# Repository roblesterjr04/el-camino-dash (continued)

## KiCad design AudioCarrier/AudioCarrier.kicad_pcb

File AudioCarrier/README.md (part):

# Audio card

A **slot card** for the DigiDash rev 2 board: **80 × 60 mm**, standing on edge in a 2×15 slot, its right-angle header
on the bottom edge and its jacks on the top edge (`docs/hardware/accessory_ports.md`, rev 2 section). It goes in
**slot 1**: the RCA block is 26.5 mm tall, and slot 1 is the one whose parts side faces off the end of the row. It is
the clock master of the slot's **I2S rail**, which reaches every other slot (an AI voice card can go in any of them). The directory keeps its old name. On it:
- an **ESP32-DevKitC-VE** (the bench board: ESP32-WROVER-E, classic ESP32 for A2DP + AVRCP + HFP; 8 MB flash, 8 MB
  PSRAM, PCB antenna) plugged into two 1 × 19 female sockets. It brings its own USB programming and 3.3 V regulator,
  so the card has no module, regulator, buttons or programming header to assemble (rev J)
- two **TI PCM5102A** stereo DACs (front pair, rear pair)
- a **TI PCM1808** ADC with an electret microphone preamp (hands-free calls)
- a **2 × 2 right-angle RCA block** (Kycon KLP42X-61-WW/RR) and, beside it on the same top edge, a small
  **3.5 mm jack** (Same Sky SJ1-3533NG, through-hole) for a hands-free car microphone (no line / aux input)
- a **74LVC125** that puts the I2S clocks, the mic data and MCLK on the slot's link lines, for the partner card

CAN node from its slot (`0x14 + (slot − 1)`: `0x14` in slot 1), 5 V from the slot only. It fits rev 2 only (the 2×5 rev 1 version is in git history).

| Files | |
| --- | --- |
| `AudioCarrier.kicad_sch` / `.kicad_pcb` / `.kicad_pro` | The card: 80 × 60 mm, 2 layers, every part on the top. Placed and routed (see [Status](#status)). KiCad 10 |
| `AudioCarrier.pretty` | The DevKitC socket footprint (pin positions and numbers as Espressif's own `Espressif.pretty/ESP32-DevKitC`, rows 25.4 mm apart) and the RCA block (hole pattern from Kycon's KLP42X-61-xx/xx drawing), and a plain 3D model of the block. Everything else is stock KiCad (the jack: `Connector_Audio:Jack_3.5mm_CUI_SJ1-3533NG_Horizontal`) |
| `generate/` | Scripts that produced the files (`gen_footprints.py`, `gen_sch.py`, `gen_pcb.py`, `drc.py`) |

## Signal paths

```
ESP32 I2S0 (master) BCK GPIO14, WS GPIO25, DOUT GPIO27 ──► PCM5102A front ──► 470 R + 2.2 nF ──► J2 FL, J3 FR
ESP32 I2S1 (slave, same BCK / WS)  DOUT GPIO26            ──► PCM5102A rear  ──► 470 R + 2.2 nF ──► J4 RL, J5 RR
+5VA ─ 1k ─ MICV (47u) ─ 2.2k ─┐
J6 tip, electret mic (100p) ────┴ 1u ─ TLV9062 A (gain 22.4) ─ 1u ─► PCM1808 VINL ──► ESP32 I2S0 DIN GPIO35
J6 ring + sleeve = GND;  PCM1808 VINR ─ 1u ─ GND;  TLV9062 B = follower on VMID (spare)
ESP32 GPIO0 (CLK_OUT) 12.288 MHz = 256 fS master clock ──► 33 R ──► PCM1808 SCKI   GPIO4 = DAC mute (XSMT, pulled low)

I2S rail (bused to all six slots), through U8 74LVC125 (enabled by GPIO21 low) and 33 R each. The card's net names
are LINK0-4; on the main board they are the rail's I2S_* nets:
  BCK ──► LINK0 = I2S_BCK    WS ──► LINK1 = I2S_WS    PCM1808 DOUT (mic) ──► LINK2 = I2S_MIC    MCLK ──► LINK4 = I2S_MCLK
  LINK3 = I2S_RET (the granted card's audio) ── 33 R ──► GPIO34 = I2S1 data in (100k pull-down)
Audio bus: FL_LINE / FR_LINE ── 100 R ──► AUDIO_L / AUDIO_R;  AUDIO_GND ── 10 R ── GND
Slot ID (pin 11): 10k to 3.3 V here, the slot's resistor to GND on the main board ──► GPIO36 (ADC1)
```

DevKitC-VE socket pins (U1; numbers as Espressif's KiCad symbol, `ESP32-DevKitC`). The GPIOs are the ones the
module version used, so the firmware's pin defines are unchanged:

| Pin | DevKitC | Net | Pin | DevKitC | Net |
| --- | --- | --- | --- | --- | --- |
| 1 | 3V3 | +3V3 (out of the DevKitC's regulator) | 19 | 5V | +5V from the slot |
| 14, 32, 38 | GND | GND | 25 | IO0 | MCLK (CLK_OUT1) → 33 R → PCM1808 SCKI, LINK4 (also the DevKitC BOOT strap) |
| 3 | VP (IO36) | SLOT_ID (ADC1) | 26 | IO4 | DAC_MUTE (XSMT, 100k down) |
| 5 | IO34 | LINK_SDIN (I2S1 data in, RET) | 33 | IO21 | LINK_EN_N (74LVC125 OEs, 10k up) |
| 6 | IO35 | ADC_DOUT (I2S0 data in) | 7 / 8 | IO32 / IO33 | CAN TXD / RXD (1k) |
| 9 | IO25 | I2S WS (both DACs, ADC, LINK1) | 10 | IO26 | I2S1 DOUT → rear DAC |
| 11 / 12 | IO27 / IO14 | I2S0 DOUT → front DAC / BCK (all, LINK0) | others | | open (EN, VN, 12, 13, 2, 5, 15, 18, 19, 22, 23, TX / RX; 6-11 flash, 16 / 17 PSRAM) |

| Jack (J2, the block) | Signal | Insert colour |
| --- | --- | --- |
| Left column, top | Front left (U5 OUTL) | white |
| Left column, bottom | Front right (U5 OUTR) | red |
| Right column, top | Rear left (U6 OUTL) | white |
| Right column, bottom | Rear right (U6 OUTR) | red |
| J6, 3.5 mm jack (Same Sky SJ1-3533NG) | tip = mic (pin T); ring (R) and sleeve (S) = GND, so a mono TS plug and a TRS plug both work | top edge, right of the block |

"Left" and "right" are seen from the plug side, standing outside the right edge. The sleeves and the front plate's two
solder tabs are ground.

- **DACs:** 3-wire I2S, SCK tied to ground so the internal PLL runs from BCK (BCK must be 64 fS, which is what the ESP32
  produces with 32-bit slots). FMT, FLT and DEMP low. Outputs are ground-centred 2.1 Vrms: no DC-block caps, just the
  datasheet's 470 R / 2.2 nF filter. The two DACs share BCK and LRCK and have their own data lines, so front and rear are
  independent (fader in software). Both stay muted until the firmware raises GPIO4. Decoupling as in the datasheet
  (LDOO 0.1 µF).
- **ADC:** slave mode (MD0 = MD1 = low), I2S 24-bit, 5 V analog / 3.3 V digital, full scale 3 Vp-p. It runs from the same
  BCK / LRCK as the DACs, so ESP32 I2S0 does full duplex (play + record) in master mode.
- **Mic input (calls only):** for an electret car hands-free microphone on a mono 3.5 mm TS plug ("plug-in power").
  Bias: 2.2 kΩ to the tip from MICV, which is +5VA through 1 kΩ + 47 µF (about 3 Hz; about 4.5 V at a 0.5 mA
  capsule). 100 pF from the tip to ground at the jack (RF). DC-blocked (1 µF into 100 kΩ to VMID = 2.5 V), then
  TLV9062 A non-inverting, gain 1 + 47k / 2.2k = 22.4 (27 dB; 2.2 kΩ + 10 µF to ground, so DC gain 1; 100 pF across
  the 47k, about 34 kHz). A -42 dBV/Pa capsule gives 0.18 Vrms at 94 dB SPL; the PCM1808's ~1 Vrms full scale is
  reached at about 109 dB SPL, so a loud voice close to the mic still has headroom. Out through 1 µF to VINL (the
  left channel, which the firmware reads). VINR is AC-grounded through 1 µF; TLV9062 B is a follower on VMID, its
  output unloaded (no floating inputs). There is no line / aux input.
- **Power:** +5 V from the port to the DevKitC's 5V pin (10 µF at the header). The DevKitC's own 3.3 V regulator
  runs the ESP32 and, from its 3V3 pin (100 nF there), the card's 3.3 V loads: the converters' digital sides, the
  buffer and the CAN VIO, some tens of mA. Ferrites make +5VA (ADC analog, op-amp, mic bias) and +3V3A (DAC analog
  and charge pump). **Do not plug the DevKitC's USB in while the card is powered from the slot**: both feed its 5V
  pin (check the DevKitC's schematic for a diode before relying on it). To program it in place, unpower the card.

## Board

- **Outline:** 80 × 60 mm, no mounting holes: the slot and the case hold it. The RCA block's plate has a hole in the
  middle of the four jacks; if it takes a screw to the case panel, plug forces go to the case and not the slot (check
  on the part: Kycon's drawing does not say).
- **Slot header (J1):** right-angle 2×15 (`PinHeader_2x15_P2.54mm_Horizontal`) on the parts side, centred on the bottom
  edge: pin 1 is 17.78 mm right of the centre (seen from the parts side, top edge up), the pins count to the left, the
  plastic body's outer face is on the bottom edge and the pins stand 6 mm past it. `gen_pcb.py` checks the orientation
  from the pads, so each pin meets the same-numbered pad of the main board's slot socket.
- **Top edge** (the case panel), from the left: the RCA block (centred at x 48, x 30.1–65.9 with its tabs) and the
  3.5 mm jack (x 72.3). These positions are constants at the top of `gen_pcb.py`; move them to suit the case.
- **DevKitC (U1):** two 1 × 19 female sockets (8.5 mm), rows 25.4 mm apart, lying along the card: pin 1 (3V3) at
  x 13.5, y 39.4, the J2 row (pins 1–19) at y 39.4 and the J3 row at y 14.0, from x 13.5 to 59.2. The DevKitC's PCB
  spans y ≈ 12.5–40.9; its **antenna end is at the left edge** and its **USB end points right** (x ≈ 61), over the
  DACs. It stands about 8.5 mm up on the sockets (module top ≈ 13.5 mm off the card, the USB plug higher), so low SMD
  parts sit under it. The module and its antenna reach past pin 1 toward the left edge: the footprint allows 13 mm
  (measure the -VE: Espressif's footprint shows the WROOM antenna 1.1–7.0 mm past pin 1), and the card keeps **no
  copper on either layer** from the left edge to x 12, y 12–41.5. Keep metal out of that end of the case. Housing: the
  card's left edge is board y 93, so the antenna is at y ≈ 81–93, z ≈ 22–55 (was the WROVER at the top corner).
- **RCA block (J2):** Kycon KLP42X-61-WW/RR (white on top, red below). The jacks face off the top edge (right-angle),
  and the plate's rear face is the board edge. The body is 34 mm wide and 10 mm deep behind the edge, and **26.5 mm
  tall** above the card (jack centres 6.7 and 20.7 mm up, columns 18 mm apart). The 1.0 mm plate and the barrels
  (7.8 mm) stand out past the edge. From the drawing (depths from the plate's front face): sleeve pins 1 / 4 at 7.0 mm,
  lower tips 3 / 6 at 10.25 mm, upper tips 2 / 5 at 11.5 mm, each column's pins 4 mm apart; two snap-in side tabs
  (2.4 mm wide, 7.5 mm deep, ±16.5 mm, barb to ±17.6 mm) in 1.9 × 3.0 mm slots, tied to ground. No switch contacts.
- **Mic jack (J6):** Same Sky SJ1-3533NG, through-hole, soldered by hand (KiCad's stock footprint, pins T / R / S),
  right of the block on the same edge. Its front face is on the edge (1.2 mm before the sleeve pin), body x 67.4–75.6
  and 14 mm deep behind the edge, its nose past the edge centred at x 72.3, where the SMT jack's was. It replaced the
  SJ-3523-SMT on 2026-11-19 so the card's connectors are all through-hole; the board was edited in place (footprint
  swapped, the jack's ground fan-outs dropped since its pins reach both pours, the tip re-routed on B to the old via).
- **Parts side (F):** every part. The DACs, ADC and op-amp sit right of the DevKitC's USB end (x 61–80), the CAN
  transceiver and the link buffer above the slot header, passives where the placer put them (some under the DevKitC).
- **Back (B):** copper and silkscreen only, no parts.
- **Assembly:** the fab places the SMD parts (one side). The through-hole parts (J1, J2, J6 and the two DevKitC sockets)
  are soldered by hand. They are marked **DNP** in the schematic and on the board (`DNP` in `gen_sch.py` /
  `gen_pcb.py`), so they stay out of the placement files, and the PCBWay BOM lists them as DNP lines
  ("do not place or buy").
- **Layers:** 2. F signal + GND pour, B GND pour + signal. 0.2 mm tracks, 0.3 mm on the supplies, 0.13 mm clearance,
  0.6 / 0.3 mm vias. Every SMD ground pin has its own via to the B pour; stitching vias tie the pours together.
- **Solder-mask dams:** U3 (VSSOP-8, 0.65 mm) has its pads narrowed to 0.43 mm so the gaps are 0.22 mm, enough for
  PCBWay to keep a mask dam (they rejected 0.15 mm on 2026-11-19). The TSSOPs are 0.25 mm as drawn. Run
  `python3 ../tools/mask_dams.py AudioCarrier` again after any regenerate (it is lost otherwise).

## Status

**Rev J (2026-11-19): the bench DevKitC-VE in sockets, 2 layers.** The WROVER-E module, the AP7361C regulator and
its capacitors (C1, C3), the module decoupling (C8, C9), the EN / BOOT parts (R2, R3, C10, SW1, SW2), the programming
header J10 and the unused node straps JP1 / JP2 are gone; the other reference numbers are unchanged. GPIO0's net is
now MCLK (was BOOT). Re-placed and re-routed by `gen_pcb.py --route` (GND left out of the router: the pours and
per-pin vias join it), then `mask_dams.py`, fill, DRC with the parity check: **0 errors, 0 unconnected**, 21
silkscreen warnings and U3's footprint-differs-from-library (the narrowed pads). 590 vias (64 GND fan-outs, 493
stitching), 109 track segments on B. Ten router vias 0.06–0.15 mm from an SMD pad were then nudged by hand (≤ 0.1 mm)
to ≥ 0.15 mm, PCBWay's via-off-pad rule; re-running `--route` does not reproduce that. Nothing in the antenna keep-out. The rev I notes that follow describe the
module version (in git).

**Schematic: done** (the slot card, 90 parts). **PCB: placed and routed** (2026-10-23, rev G): 80 × 60 mm, 4 layers, 90
placed parts (88 in the placement file: JP1 / JP2 are copper only). DRC with the schematic parity check: **no errors,
nothing unconnected, no footprint / parity errors**; 28 silkscreen warnings (text at the edge, over pads, overlapping) and one footprint-differs-from-library warning (U3, the mask-dam pads).
Rev H (2026-10-27): every part on F (single-sided assembly), re-placed and re-routed by `gen_pcb.py --route`
(120 passes); the ground stitching closed the one link Freerouting left. Two fan-out vias (R17 pad 2, R25 pad 1)
were then moved by hand to 0.15 mm clear of their pads, the PCBWay via-off-pad rule. 550 vias, none touching a pad;
nothing in the antenna keep-out. Fab outputs in `fab/`
(`python3 ../tools/fab_export.py AudioCarrier`); `fab/AudioCarrier_BOM_PCBWay.csv` is kept by hand and matches the
placement file; `AudioCarrier_BOM.csv` is the same list.
Rev I (2026-10-27): RCA block **Switchcraft PJRAS2X2S01X → Kycon KLP42X-61-WW/RR** (34 mm wide, 6 pins + 2 snap-in
tabs, 26.5 mm tall), centred at x 48 (was 52) so it clears the jack; re-placed and re-routed by `gen_pcb.py --route`.
Freerouting left /EN, /I2S_LRC and U8 pin 7 (GND) open and the finisher could not join them, so they were finished
by a one-off grid router (not in `generate/`): /EN a 5.5 mm F track by SW1; /I2S_LRC from U5 pin 15 through two vias
to U6's side, after lifting U5 pin 16's GND fan-out stub (pin 16 reaches the pours without it); U8 pin 7 a track and
a via to the plane. Ten Freerouting vias 0.137–0.146 mm from a pad were nudged (≤ 0.02 mm) to ≥ 0.15 mm, the PCBWay
via-off-pad rule. DRC with the parity check: **0 errors, 0 unconnected**, 28 silkscreen warnings; 546 vias, none
within 0.15 mm of a pad. Re-running `gen_pcb.py --route` does not reproduce these fixes. The finisher now checks
clearance only against items near each join (it hung for 20+ minutes on the full board).

- **Rev G (2026-10-23), before the PCBWay order:**
  - **Module:** ESP32-PICO-MINI-02-N8R2 (NRND) → **ESP32-WROVER-E-N8R8**. Footprint drawn from the datasheet v2.4
    (figure 15: 38 pads 1.5 × 0.9 on 1.27 mm, centres 17.5 mm apart, pin 1 7.44 mm from the antenna end, pin 19 1.1 mm
    from the far end; EPAD 3.7 mm square, 7.5 mm from the left edge and 16.16 mm from the far end, nine 0.9 mm paste
    openings, no vias in it). Pins checked against table 3. Same GPIOs as before (pin map above).
  - **Regulator:** AMS1117-3.3 + 22 µF tantalum → **AP7361C-33E-13** with ceramics (pinout 1 IN, 2 GND, 3 OUT, from
    the Diodes datasheet); tab solid to a ground copper area with 12 vias.
  - **Mic:** aux path removed (ring buffer, its coupling cap and bias resistor, the RING net); bias now from +5VA
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
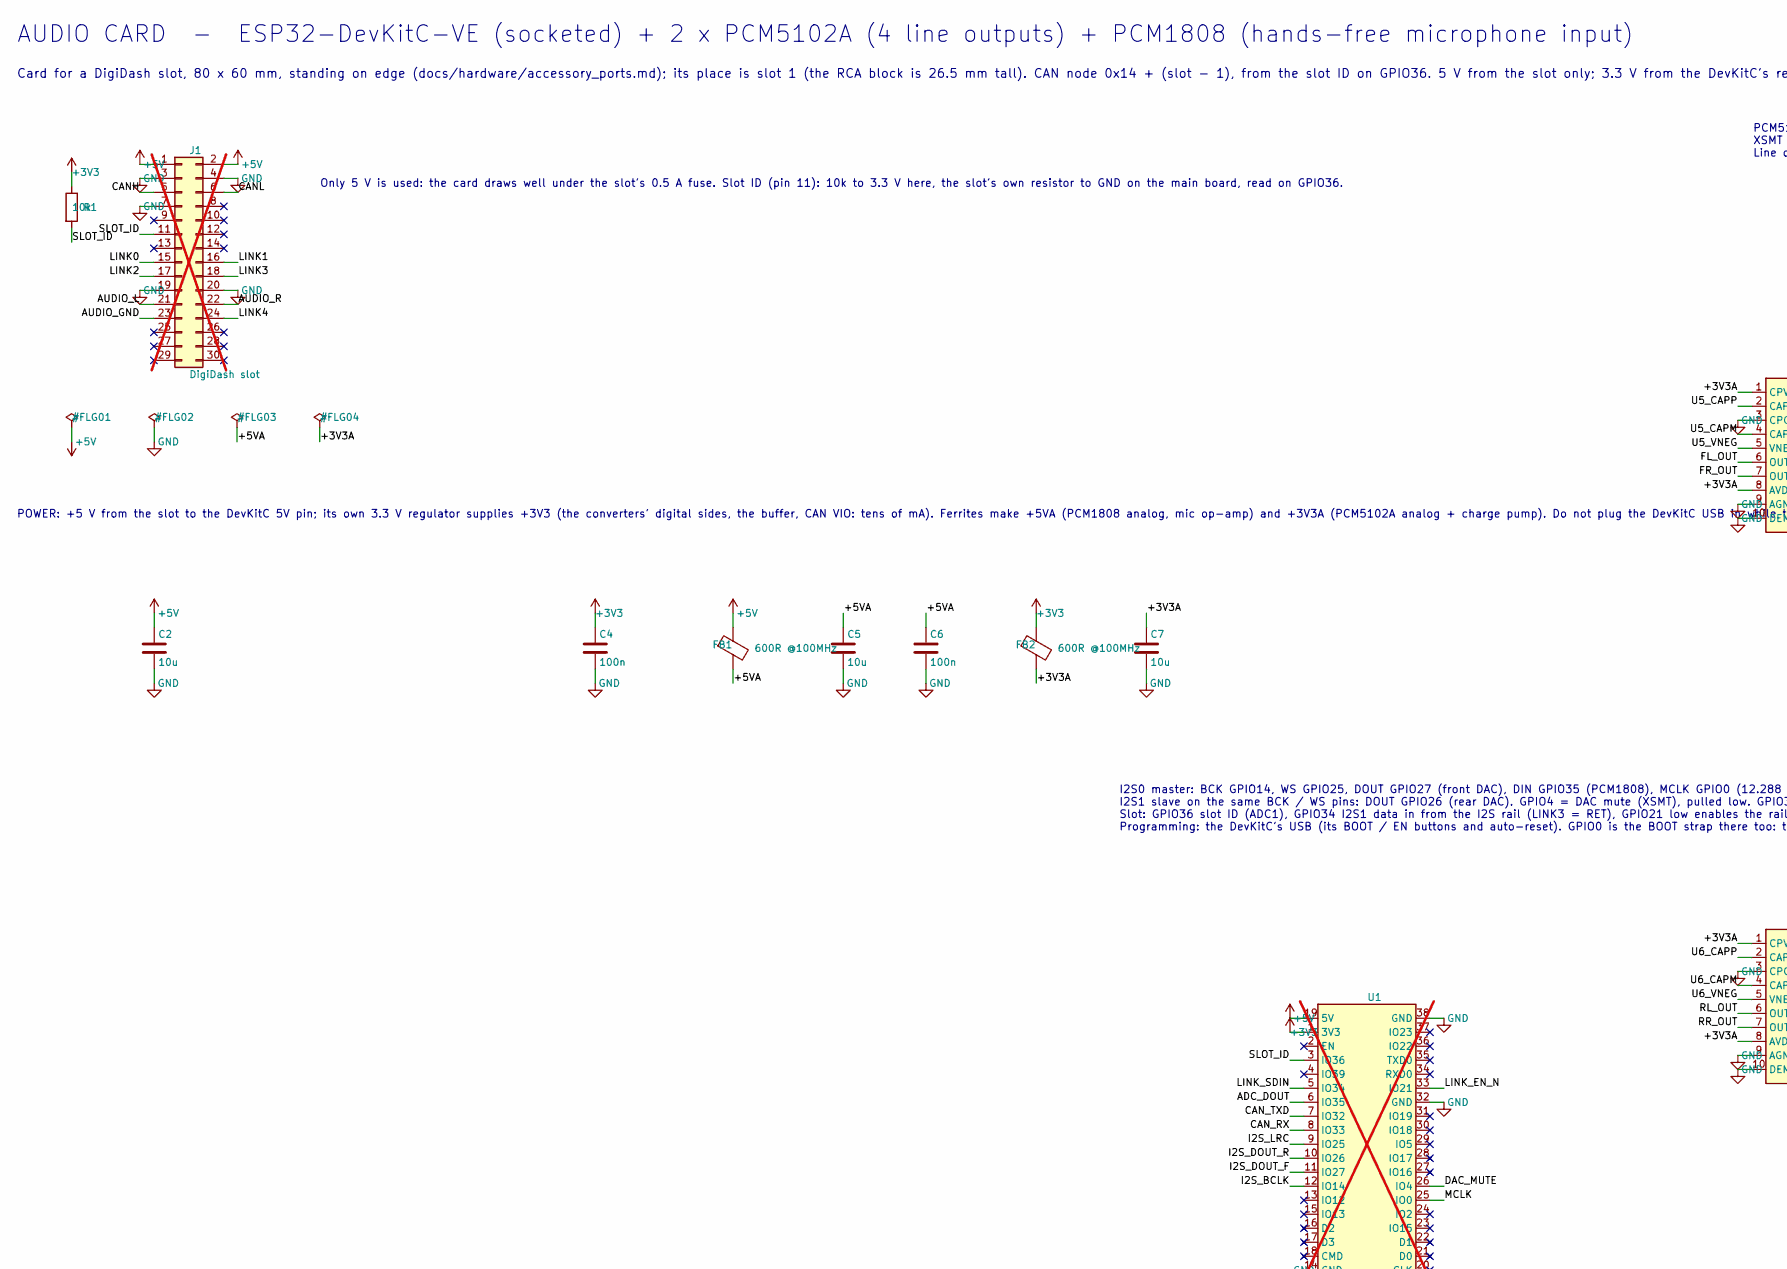
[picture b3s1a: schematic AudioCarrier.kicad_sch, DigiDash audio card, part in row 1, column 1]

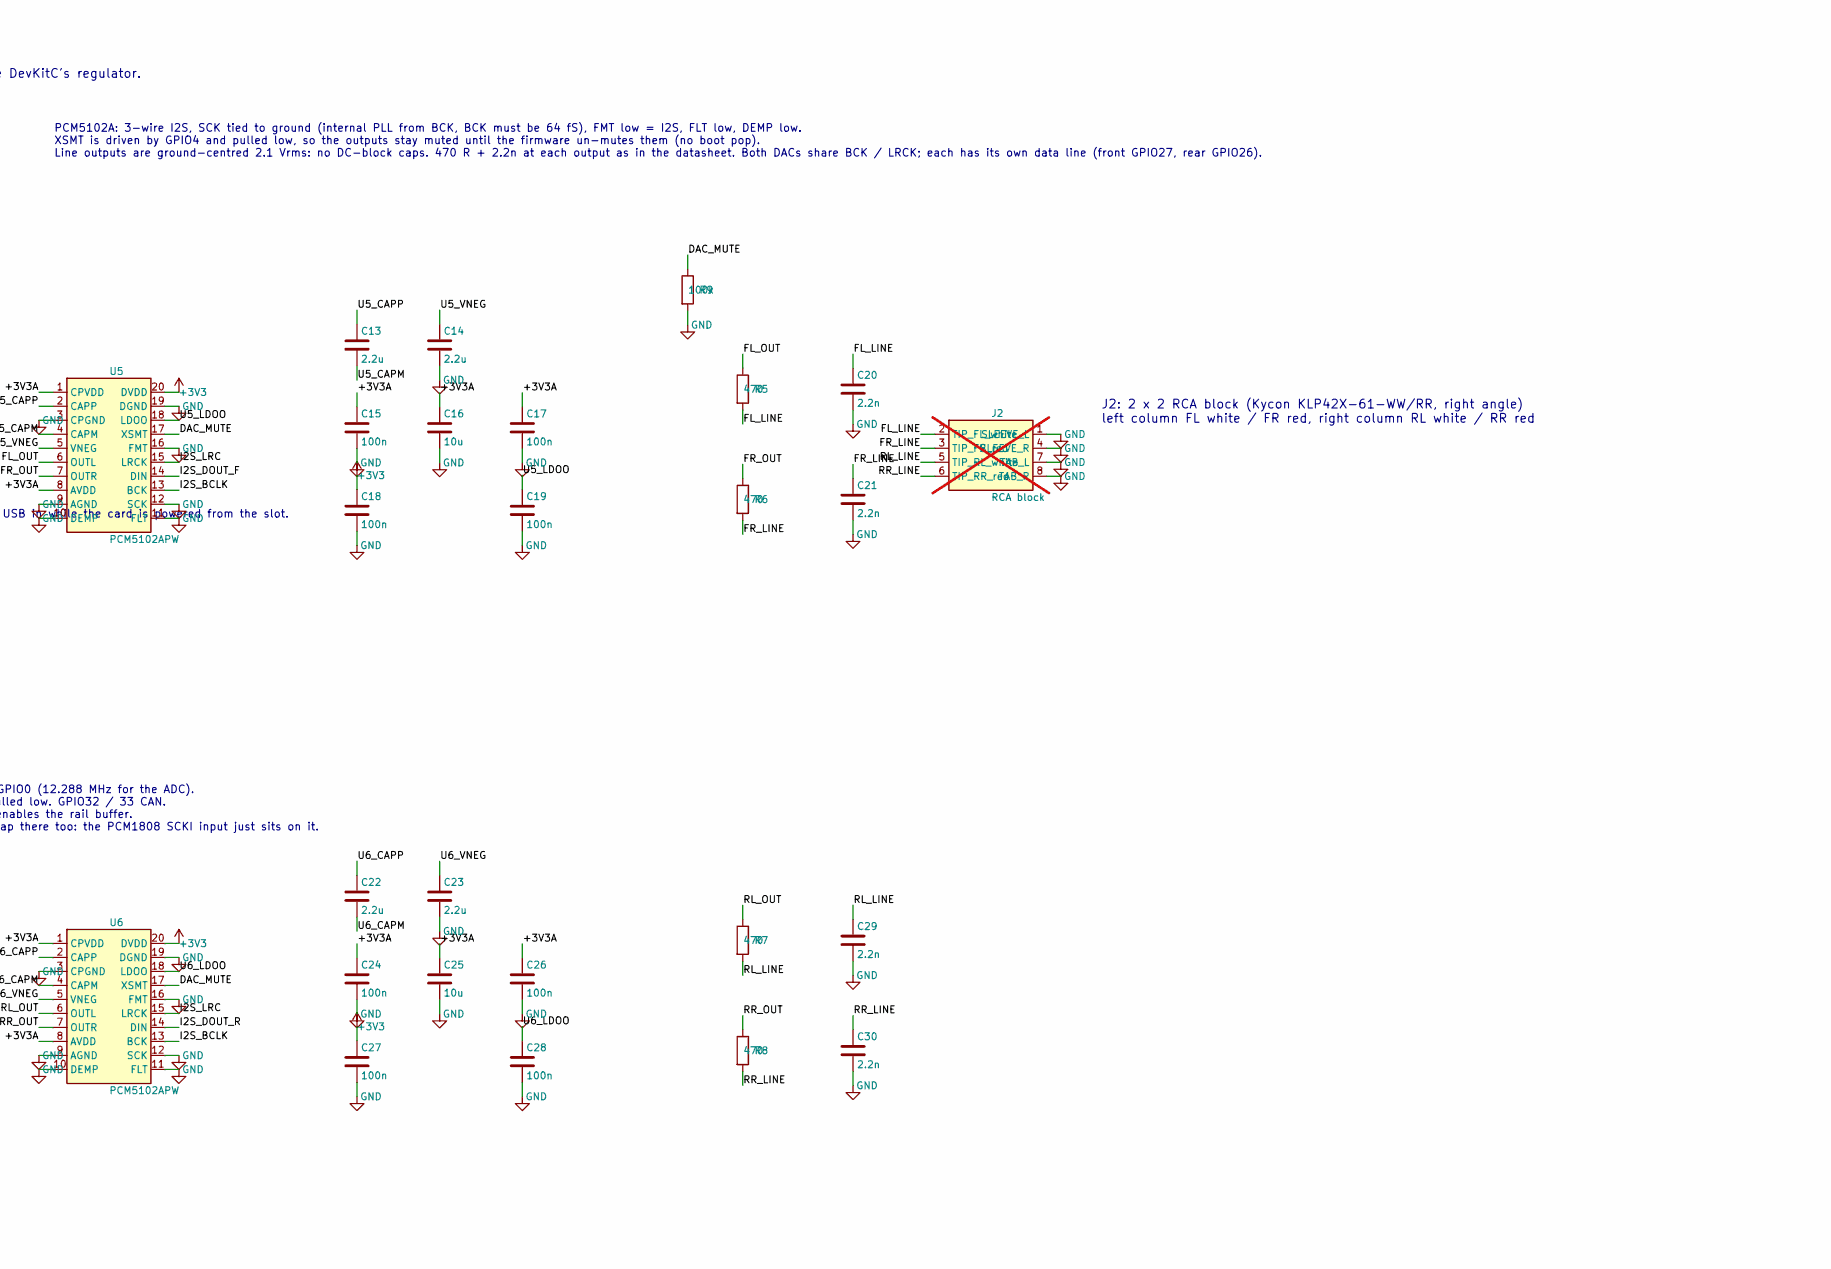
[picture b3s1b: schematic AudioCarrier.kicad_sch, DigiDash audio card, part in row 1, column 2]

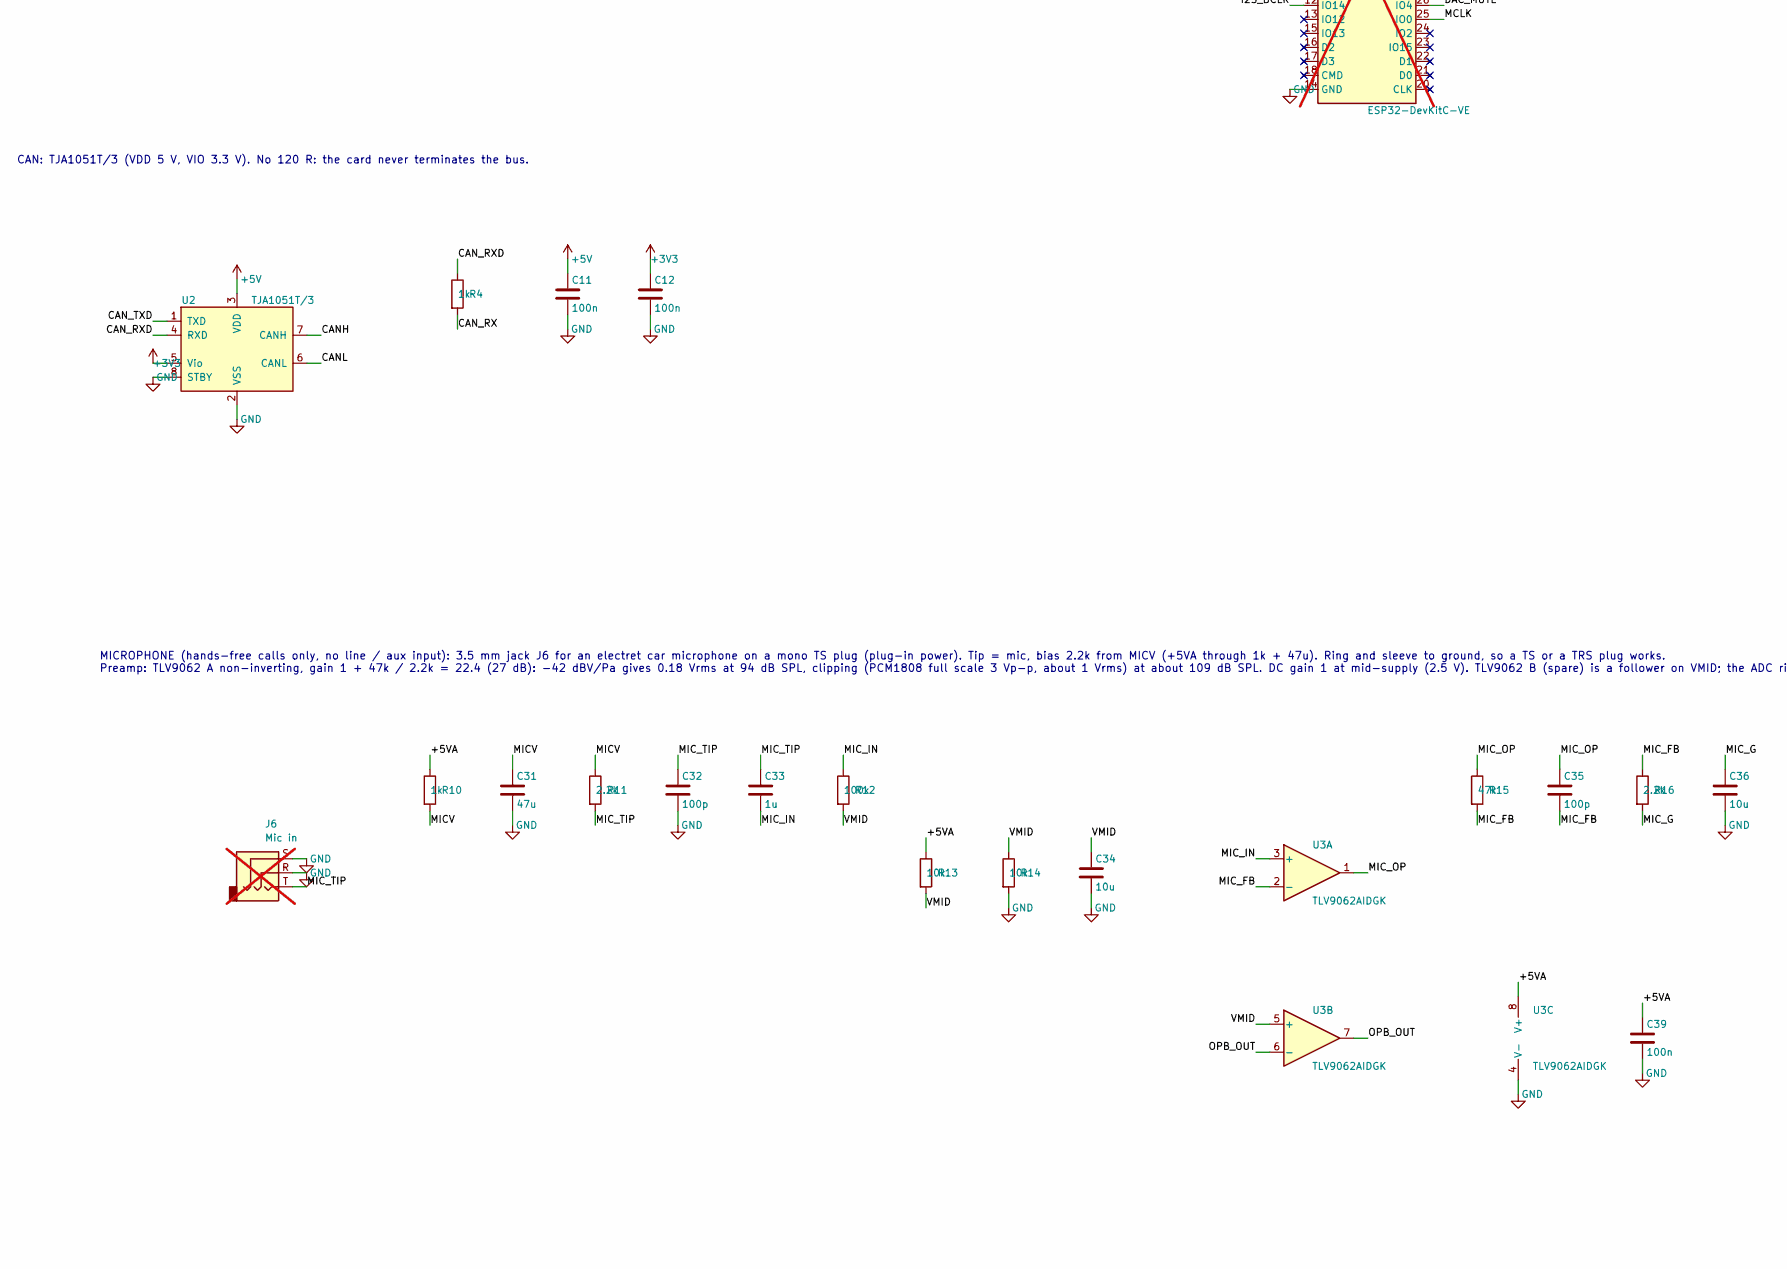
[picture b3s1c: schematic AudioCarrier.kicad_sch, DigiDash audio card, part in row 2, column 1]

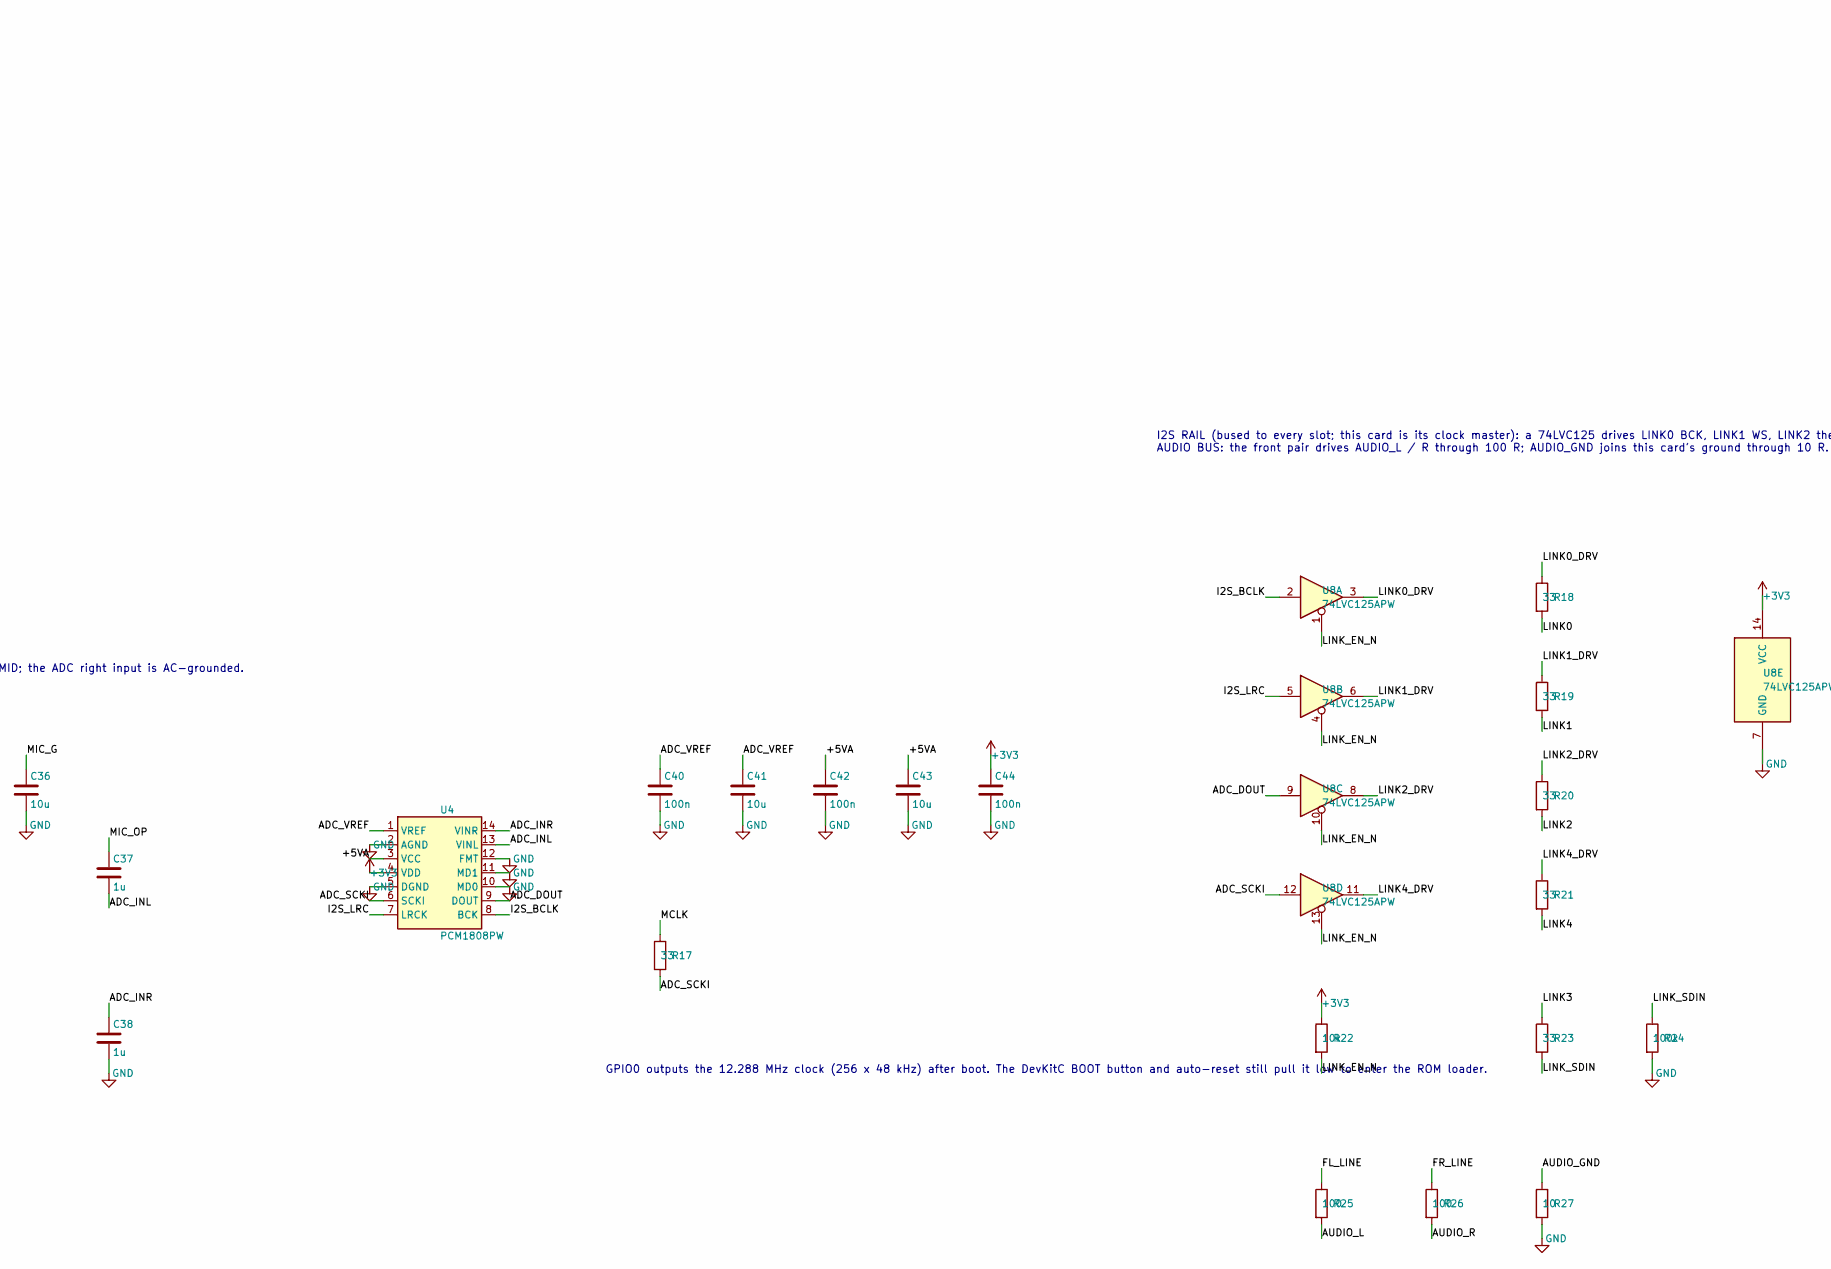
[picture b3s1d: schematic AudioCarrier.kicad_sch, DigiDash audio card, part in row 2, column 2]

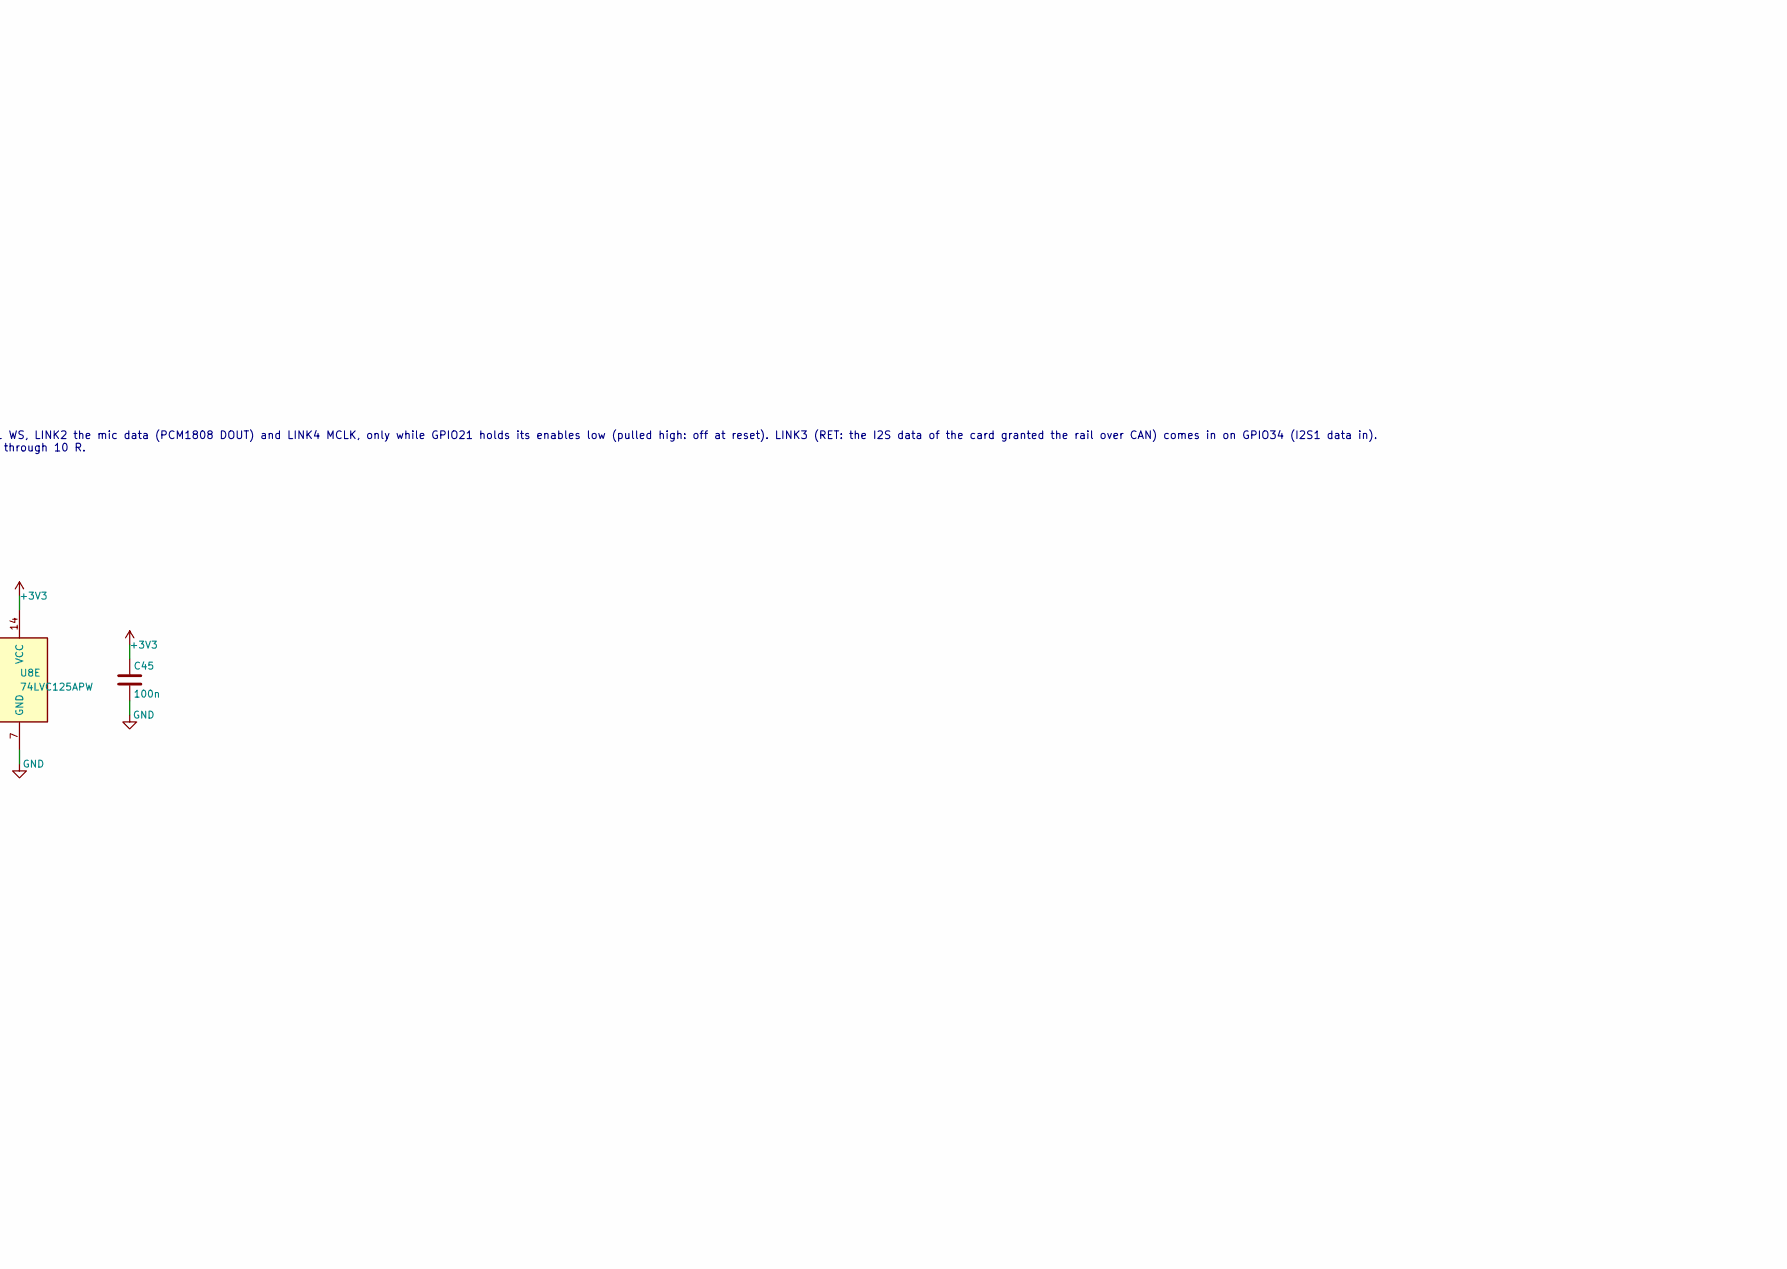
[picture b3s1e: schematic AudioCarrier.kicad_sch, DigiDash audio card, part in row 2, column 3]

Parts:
C2, C5, C7, C16, C25, C34, C36, C41, C43: 10u; C_0603_1608Metric
C4, C6, C11, C12, C15, C17, C18, C19, C24, C26, C27, C28, C39, C40, C42, C44, C45: 100n; C_0603_1608Metric
C13, C14, C22, C23: 2.2u; C_0603_1608Metric
C20, C21, C29, C30: 2.2n; C_0603_1608Metric
C31: 47u; C_1206_3216Metric
C32, C35: 100p; C_0603_1608Metric
C33, C37, C38: 1u; C_0603_1608Metric
FB1, FB2: 600R @100MHz; L_0603_1608Metric
J1: DigiDash slot; PinHeader_2x15_P2.54mm_Horizontal; not fitted
J2: RCA block; RCA_Kycon_KLP42X-61_RightAngle; not fitted
J6: Mic in; Jack_3.5mm_CUI_SJ1-3533NG_Horizontal; not fitted
R1, R13, R14, R22: 10k; R_0603_1608Metric
R4, R10: 1k; R_0603_1608Metric
R5, R6, R7, R8: 470; R_0603_1608Metric
R9, R12, R24: 100k; R_0603_1608Metric
R11, R16: 2.2k; R_0603_1608Metric
R15: 47k; R_0603_1608Metric
R17, R18, R19, R20, R21, R23: 33; R_0603_1608Metric
R25, R26: 100; R_0603_1608Metric
R27: 10; R_0603_1608Metric
U1: ESP32-DevKitC-VE; ESP32-DevKitC_Socket; not fitted
U2: TJA1051T/3; SOIC-8_3.9x4.9mm_P1.27mm
U3: TLV9062AIDGK; VSSOP-8_3x3mm_P0.65mm
U4: PCM1808PW; TSSOP-14_4.4x5mm_P0.65mm
U5, U6: PCM5102APW; TSSOP-20_4.4x6.5mm_P0.65mm
U8: 74LVC125APW; TSSOP-14_4.4x5mm_P0.65mm

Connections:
+3V3: C4.1, C12.1, C18.1, C27.1, C44.1, C45.1, FB2.1, R1.1, R22.1, U1.1 (3V3), U2.5 (Vio), U4.4 (VDD), U5.20 (DVDD), U6.20 (DVDD), U8.14 (VCC)
+5V: C2.1, C11.1, FB1.1, J1.1, J1.2, U1.19 (5V), U2.3 (VDD)
/+3V3A: C7.1, C15.1, C16.1, C17.1, C24.1, C25.1, C26.1, FB2.2, U5.1 (CPVDD), U5.8 (AVDD), U6.1 (CPVDD), U6.8 (AVDD)
/+5VA: C5.1, C6.1, C39.1, C42.1, C43.1, FB1.2, R10.1, R13.1, U3.8 (V+), U4.3 (VCC)
/ADC_DOUT: U1.6 (IO35), U4.9 (DOUT), U8.9
/ADC_INL: C37.2, U4.13 (VINL)
/ADC_INR: C38.1, U4.14 (VINR)
/ADC_SCKI: R17.2, U4.6 (SCKI), U8.12
/ADC_VREF: C40.1, C41.1, U4.1 (VREF)
/AUDIO_GND: J1.23, R27.1
/AUDIO_L: J1.21, R25.2
/AUDIO_R: J1.22, R26.2
/CANH: J1.5, U2.7 (CANH)
/CANL: J1.6, U2.6 (CANL)
/CAN_RX: R4.2, U1.8 (IO33)
/CAN_RXD: R4.1, U2.4 (RXD)
/CAN_TXD: U1.7 (IO32), U2.1 (TXD)
/DAC_MUTE: R9.1, U1.26 (IO4), U5.17 (XSMT), U6.17 (XSMT)
/FL_LINE: C20.1, J2.2 (TIP_FL_white), R5.2, R25.1
/FL_OUT: R5.1, U5.6 (OUTL)
/FR_LINE: C21.1, J2.3 (TIP_FR_red), R6.2, R26.1
/FR_OUT: R6.1, U5.7 (OUTR)
/I2S_BCLK: U1.12 (IO14), U4.8 (BCK), U5.13 (BCK), U6.13 (BCK), U8.2
/I2S_DOUT_F: U1.11 (IO27), U5.14 (DIN)
/I2S_DOUT_R: U1.10 (IO26), U6.14 (DIN)
/I2S_LRC: U1.9 (IO25), U4.7 (LRCK), U5.15 (LRCK), U6.15 (LRCK), U8.5
/LINK0: J1.15, R18.2
/LINK0_DRV: R18.1, U8.3
/LINK1: J1.16, R19.2
/LINK1_DRV: R19.1, U8.6
/LINK2: J1.17, R20.2
/LINK2_DRV: R20.1, U8.8
/LINK3: J1.18, R23.1
/LINK4: J1.24, R21.2
/LINK4_DRV: R21.1, U8.11
/LINK_EN_N: R22.2, U1.33 (IO21), U8.1, U8.4, U8.10, U8.13
/LINK_SDIN: R23.2, R24.1, U1.5 (IO34)
/MCLK: R17.1, U1.25 (IO0)
/MICV: C31.1, R10.2, R11.1
/MIC_FB: C35.2, R15.2, R16.1, U3.2 (-)
/MIC_G: C36.1, R16.2
/MIC_IN: C33.2, R12.1, U3.3 (+)
/MIC_OP: C35.1, C37.1, R15.1, U3.1
/MIC_TIP: C32.1, C33.1, J6.T, R11.2
/OPB_OUT: U3.6 (-), U3.7
/RL_LINE: C29.1, J2.5 (TIP_RL_white), R7.2
/RL_OUT: R7.1, U6.6 (OUTL)
/RR_LINE: C30.1, J2.6 (TIP_RR_red), R8.2
/RR_OUT: R8.1, U6.7 (OUTR)
/SLOT_ID: J1.11, R1.2, U1.3 (IO36)
/U5_CAPM: C13.2, U5.4 (CAPM)
/U5_CAPP: C13.1, U5.2 (CAPP)
/U5_LDOO: C19.1, U5.18 (LDOO)
/U5_VNEG: C14.1, U5.5 (VNEG)
/U6_CAPM: C22.2, U6.4 (CAPM)
/U6_CAPP: C22.1, U6.2 (CAPP)
/U6_LDOO: C28.1, U6.18 (LDOO)
/U6_VNEG: C23.1, U6.5 (VNEG)
/VMID: C34.1, R12.2, R13.2, R14.1, U3.5 (+)
GND: C2.2, C4.2, C5.2, C6.2, C7.2, C11.2, C12.2, C14.2, C15.2, C16.2, C17.2, C18.2, C19.2, C20.2, C21.2, C23.2, C24.2, C25.2, C26.2, C27.2, C28.2, C29.2, C30.2, C31.2, C32.2, C34.2, C36.2, C38.2, C39.2, C40.2, C41.2, C42.2, C43.2, C44.2, C45.2, J1.3, J1.4, J1.7, J1.19, J1.20, J2.1 (SLEEVE_L), J2.4 (SLEEVE_R), J2.7 (TAB_L), J2.8 (TAB_R), J6.R, J6.S, R9.2, R14.2, R24.2, R27.2, U1.14 (GND), U1.32 (GND), U1.38 (GND), U2.2 (VSS), U2.8 (STBY), U3.4 (V-), U4.2 (AGND), U4.5 (DGND), U4.10 (MD0), U4.11 (MD1), U4.12 (FMT), U5.3 (CPGND), U5.9 (AGND), U5.10 (DEMP), U5.11 (FLT), U5.12 (SCK), U5.16 (FMT), U5.19 (DGND), U6.3 (CPGND), U6.9 (AGND), U6.10 (DEMP), U6.11 (FLT), U6.12 (SCK), U6.16 (FMT), U6.19 (DGND), U8.7 (GND)

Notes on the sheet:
AUDIO CARD - ESP32-DevKitC-VE (socketed) + 2 x PCM5102A (4 line outputs) + PCM1808 (hands-free microphone input)
Card for a DigiDash slot, 80 x 60 mm, standing on edge (docs/hardware/accessory_ports.md); its place is slot 1 (the RCA block is 26.5 mm tall). CAN node 0x14 + (slot - 1), from the slot ID on GPIO36. 5 V from the slot only; 3.3 V from the DevKitC's regulator.
Only 5 V is used: the card draws well under the slot's 0.5 A fuse. Slot ID (pin 11): 10k to 3.3 V here, the slot's own resistor to GND on the main board, read on GPIO36.
POWER: +5 V from the slot to the DevKitC 5V pin; its own 3.3 V regulator supplies +3V3 (the converters' digital sides, the buffer, CAN VIO: tens of mA). Ferrites make +5VA (PCM1808 analog, mic op-amp) and +3V3A (PCM5102A analog + charge pump). Do not plug the DevKitC USB in while the card is powere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
I2S0 master: BCK GPIO14, WS GPIO25, DOUT GPIO27 (front DAC), DIN GPIO35 (PCM1808), MCLK GPIO0 (12.288 MHz for the ADC). I2S1 slave on the same BCK / WS pins: DOUT GPIO26 (rear DAC). GPIO4 = DAC mute (XSMT), pulled low. GPIO32 / 33 CAN. Slot: GPIO36 slot ID (ADC1), GPIO34 I2S1 data in from the I2S r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
CAN: TJA1051T/3 (VDD 5 V, VIO 3.3 V). No 120 R: the card never terminates the bus.
PCM5102A: 3-wire I2S, SCK tied to ground (internal PLL from BCK, BCK must be 64 fS), FMT low = I2S, FLT low, DEMP low. XSMT is driven by GPIO4 and pulled low, so the outputs stay muted until the firmware un-mutes them (no boot pop). Line outputs are ground-centred 2.1 Vrms: no DC-block caps. 470 R 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
J2: 2 x 2 RCA block (Kycon KLP42X-61-WW/RR, right angle) left column FL white / FR red, right column RL white / RR red
MICROPHONE (hands-free calls only, no line / aux input): 3.5 mm jack J6 for an electret car microphone on a mono TS plug (plug-in power). Tip = mic, bias 2.2k from MICV (+5VA through 1k + 47u). Ring and sleeve to ground, so a TS or a TRS plug works. Preamp: TLV9062 A non-inverting, gain 1 + 47k / 2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
GPIO0 outputs the 12.288 MHz clock (256 x 48 kHz) after boot. The DevKitC BOOT button and auto-reset still pull it low to enter the ROM loader.
I2S RAIL (bused to every slot; this card is its clock master): a 74LVC125 drives LINK0 BCK, LINK1 WS, LINK2 the mic data (PCM1808 DOUT) and LINK4 MCLK, only while GPIO21 holds its enables low (pulled high: off at reset). LINK3 (RET: the I2S data of the card granted the rail over CAN) comes in on GP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

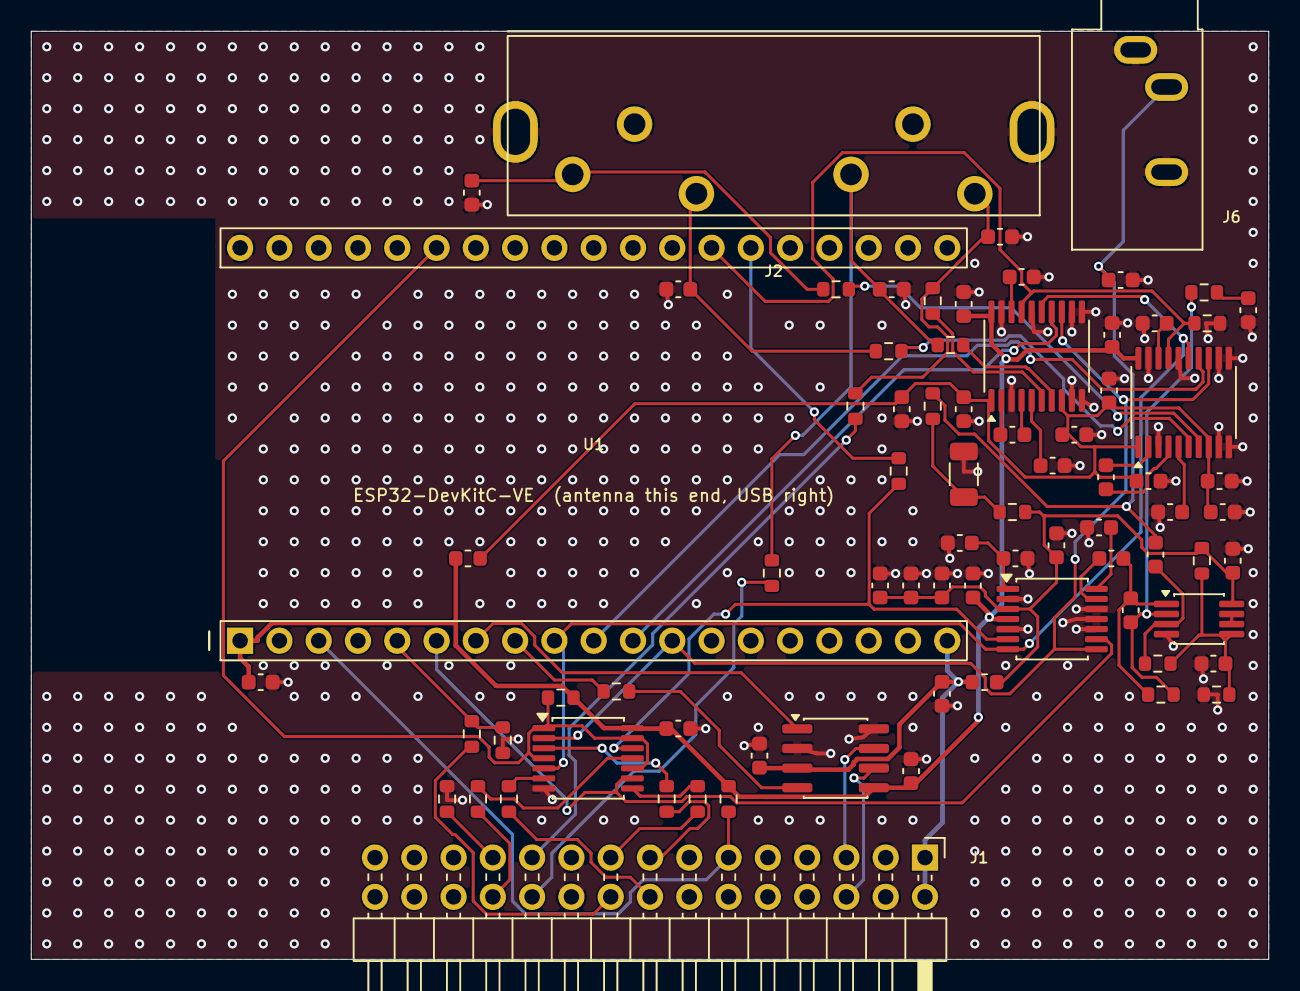
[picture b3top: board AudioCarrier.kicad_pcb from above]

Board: 2 copper layers, 80.0 x 60.0 mm, 77 parts (0 on the bottom side), 60 nets.

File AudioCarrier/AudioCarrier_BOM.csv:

Qty,Designators,Manufacturer part,Description,Package,Type,Side,Notes
9,C2 C5 C7 C16 C25 C34 C36 C41 C43,Samsung CL10A106KP8NNNC,10u: Capacitor 10u X5R 10 V,0603,SMD,Top,
17,C4 C6 C11 C12 C15 C17 C18 C19 C24 C26 C27 C28 C39 C40 C42 C44 C45,Samsung CL10B104KB8NNNC,100n: Capacitor 100n X7R 50 V,0603,SMD,Top,
3,C33 C37 C38,Samsung CL10B105KO8NNNC,1u: Capacitor 1u X7R 16 V,0603,SMD,Top,
4,C13 C14 C22 C23,Samsung CL10A225KO8NNNC,2.2u: Capacitor 2.2u X5R 16 V,0603,SMD,Top,
4,C20 C21 C29 C30,Samsung CL10C222JB8NNNC,2.2n: Capacitor 2.2n C0G 50 V,0603,SMD,Top,C0G
1,C31,Samsung CL31A476MPHNNNE,47u: Capacitor 47u X5R 10 V,1206,SMD,Top,Electret bias supply filter
2,C32 C35,Samsung CL10C101JB8NNNC,100p: Capacitor 100p C0G 50 V,0603,SMD,Top,C0G
2,FB1 FB2,Murata BLM18KG601SN1D,600R @100MHz: Ferrite bead (analog supply filters),0603,SMD,Top,"600 R @ 100 MHz, 1.3 A"
1,J1,Sullins PRPC015DBAN-M71RC,"DigiDash slot: pin header 2 x 15, 2.54 mm, right angle",THT,THT,Top,"DNP (hand-soldered). Any 2 x 15 2.54 mm right-angle male header; on the bottom edge, pins pointing off the board"
1,J2,Kycon KLP42X-61-WW/RR,"RCA block: RCA jacks, 2 x 2, right angle, white on top, red below (front L/R, rear L/R)",THT (custom footprint),THT,Top,"DNP (hand-soldered). Check against the part: board-edge line (plate rear face), side-tab slots, 26.5 mm height"
1,J6,Same Sky SJ1-3533NG,"Mic in: 3.5 mm audio jack, 3-conductor, right angle, through-hole (tip = mic, ring and sleeve = GND)",THT (Jack_3.5mm_CUI_SJ1-3533NG_Horizontal),THT,Top,"DNP (hand-soldered). Soldered by hand. Face on the top edge, nose centred at x 72.3 (as before). DigiKey CP1-3533NG-ND"
4,R1 R13 R14 R22,Yageo RC0603FR-0710KL,10k: Resistor 10k 1%,0603,SMD,Top,
2,R4 R10,Yageo RC0603FR-071KL,1k: Resistor 1k 1%,0603,SMD,Top,R10 = electret bias supply filter
4,R5 R6 R7 R8,Yageo RC0603FR-07470RL,470: Resistor 470 1%,0603,SMD,Top,DAC output filter
3,R9 R12 R24,Yageo RC0603FR-07100KL,100k: Resistor 100k 1%,0603,SMD,Top,
2,R11 R16,Yageo RC0603FR-072K2L,2.2k: Resistor 2.2k 1%,0603,SMD,Top,mic bias / preamp gain
1,R15,Yageo RC0603FR-0747KL,47k: Resistor 47k 1%,0603,SMD,Top,preamp feedback
6,R17 R18 R19 R20 R21 R23,Yageo RC0603FR-0733RL,33: Resistor 33 1%,0603,SMD,Top,link / clock series damping
2,R25 R26,Yageo RC0603FR-07100RL,100: Resistor 100 1%,0603,SMD,Top,audio bus drive
1,R27,Yageo RC0603FR-0710RL,10: Resistor 10 1%,0603,SMD,Top,audio bus ground lift
1,U2,NXP TJA1051T/3/1J,"TJA1051T/3: CAN FD transceiver (pin-compatible with MCP2562-E/SN), VDD 5 V, VIO 3.3 V",SOIC-8,SMD,Top,
1,U3,Texas Instruments TLV9062IDGKR,"TLV9062IDGK: Dual RRIO op-amp, 10 MHz, 10 nV/rtHz (mic preamp; B unused, a follower)",VSSOP-8,SMD,Top,Any RRIO dual with the standard pinout will do; pads narrowed to 0.43 mm on purpose (solder-mask dams)
1,U4,Texas Instruments PCM1808PWR,"PCM1808PW: Stereo audio ADC, 24-bit (microphone in)",TSSOP-14,SMD,Top,
2,U5 U6,Texas Instruments PCM5102APWR,"PCM5102APW: Stereo audio DAC, 32-bit, 2.1 Vrms ground-centred out",TSSOP-20,SMD,Top,"U5 front pair, U6 rear pair"
1,U8,"Nexperia 74LVC125APW,118","74LVC125APW: Quad buffer, 3-state (the slot link outputs)",TSSOP-14,SMD,Top,
2,U1,Sullins PPTC191LFBN-RC,"DevKitC sockets: female header 1 x 19, 2.54 mm, vertical, 8.5 mm (two per card, in the U1 footprint)",THT,THT,Top,"DNP (hand-soldered). Soldered by hand. Any 1 x 19 2.54 mm female socket, about 8.5 mm tall"
1,U1 (plugs in),Espressif ESP32-DevKitC-VE,"ESP32-DevKitC-VE: ESP32-WROVER-E dev board, 8 MB flash, 8 MB PSRAM (the bench board)",Plug-in board,Module,Top,"Not assembled: supplied by us, plugs into the sockets. Must be the -VE (PSRAM)"
